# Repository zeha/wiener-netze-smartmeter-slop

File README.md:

# Wiener Netze smart meter for ESPHome

An [ESPHome](https://esphome.io) external component, `wiener_netze`, that reads the
customer interface (Kundenschnittstelle) of the Wiener Netze M1 smart meter
(Iskraemeko, also Landis+Gyr E450 with the same frame layout) through its IR
window, decrypts the push telegrams and exposes the values to Home Assistant.

The meter pushes an encrypted DLMS/COSEM telegram in an HDLC frame (105 bytes)
about once per second, receive only, 9600 baud 8N1. The component:

- waits for the `7E A0` frame start and collects 105 bytes,
- checks the CRC-16/X-25 frame checksum,
- decrypts the payload with AES-128 (CTR, which is GCM without the tag check)
  using your security key; the IV is the system title (frame bytes 14..21) plus
  the frame counter (bytes 24..27) plus `00 00 00 02`,
- reads the meter time and eight registers at fixed offsets and publishes them,
- drops frames whose decrypted timestamp is not plausible (typically a wrong key),
- logs one warning if no valid telegram arrived within `read_timeout` after boot.

The logic is a port of [aldadic/esp-smartmeter-reader](https://github.com/aldadic/esp-smartmeter-reader)
(GPL-3.0); see [LICENSE](LICENSE).

## Hardware

- Wemos (LOLIN) S2 Mini: ESP32-S2, 4 MB flash, 2 MB PSRAM. ESPHome board id `lolin_s2_mini`.
- A passive IR read head (phototransistor, 3.3 V logic), e.g. the common "IR Lesekopf TTL" types.

| IR head | S2 Mini |
|---------|---------|
| VCC     | 3V3     |
| GND     | GND     |
| Data out of the head (Hichi IR TTL: yellow wire) | GPIO11 |

No TX line is needed: the meter only sends; the head's transmit input (Hichi:
green wire) stays unconnected. ESPHome enables no pull-up on the RX pin by
itself, so the config turns on the internal one (`mode: {input: true, pullup:
true}`). If nothing arrives at all, the head may output an inverted signal; set
`inverted: true` on the `rx_pin` (see the example config). With the
[power dock](hardware/power-dock/README.md) the head's supply is switched by
GPIO5 (low = on); the example config turns it on at boot. The S2 Mini logs over
its native USB port, so the hardware UART is free for the meter.

### Battery voltage divider

The example config measures the battery of the 7000 mAh LiPo:

| Part | Connection |
|------|------------|
| R1 = 1 MOhm | battery + terminal -> GPIO3 |
| R2 = 1 MOhm | GPIO3 -> GND |
| C = 100 nF (optional) | GPIO3 -> GND, against noise |

GPIO3 is on ADC1, which keeps working while WiFi is on (ADC2 does not). The
divider halves the cell voltage (4.2 V full -> 2.1 V at the pin), inside the
range of the 12 dB attenuation. Tap the battery's own + terminal, before any
regulator. Do not measure the board's 3V3 pin or rail: it is regulated, so it
reads about 3.3 V until the battery is almost empty and says nothing about the
charge. Also, never connect a LiPo (up to 4.2 V) straight to the 3V3 pin. Feed
it through a regulator to 3V3, or into the 5V/VBUS pin and the on-board LDO.

The divider draws about 2 uA continuously (4.2 V / 2 MOhm), negligible against
7000 mAh. With 1 MOhm resistors the source is high-impedance; the 100 nF
capacitor gives the ADC a stable charge to sample and makes readings noticeably
steadier.

## Configuration

See [config/example_smartmeter.yaml](config/example_smartmeter.yaml) for a complete device.

```yaml
external_components:
  - source: github://zeha/wiener-netze-smartmeter-slop@main
    components: [wiener_netze]

uart:
  id: meter_uart
  rx_pin:
    number: GPIO11
    mode:
      input: true
      pullup: true
  baud_rate: 9600

wiener_netze:
  uart_id: meter_uart
  security_key: "0123456789abcdef0123456789abcdef"  # placeholder: your key from the portal
  read_timeout: 10s        # optional, default 10s
  on_telegram:             # optional, runs after every decoded telegram
    - logger.log: "telegram"

sensor:
  - platform: wiener_netze
    type: energy_active_plus
    name: "Energy import"

text_sensor:
  - platform: wiener_netze
    type: timestamp
    name: "Meter time"
```

The security key (32 hex characters, "Schlüssel" for the customer interface) is
shown in the Wiener Netze Smart Meter portal after the interface has been
activated. Keep it in `secrets.yaml` (`security_key: !secret meter_key`).

### Sensor types

| `type` | Unit | Device class | State class |
|--------|------|--------------|-------------|
| `energy_active_plus` (+A, import) | kWh | energy | total_increasing |
| `energy_active_minus` (-A, export) | kWh | energy | total_increasing |
| `energy_reactive_plus` (+R) | kvarh | reactive_energy | total_increasing |
| `energy_reactive_minus` (-R) | kvarh | reactive_energy | total_increasing |
| `power_active_plus` (+P) | W | power | measurement |
| `power_active_minus` (-P) | W | power | measurement |
| `power_reactive_plus` (+Q) | var | reactive_power | measurement |
| `power_reactive_minus` (-Q) | var | reactive_power | measurement |
| `telegram_count` | | | total_increasing (diagnostic; resets on every boot/wake) |

Text sensor `type: timestamp` (default): meter time as `YYYY-MM-DD HH:MM:SS`
(local meter time, no time zone).

The meter sends energy in Wh/varh; the component divides by 1000, as the
reference sketch does. All of these are standard ESPHome sensors, so filters,
names and ids work as usual. ESPHome sensor values are 32-bit floats: above
about 16 777 kWh the import counter loses its last Wh digit.

## Battery operation

The example sleeps with `deep_sleep` and wakes every 5 minutes (`sleep_duration`;
1 to 10 minutes are sensible). One telegram per wake-up is enough since the
meter pushes about every second. The `on_telegram` automation waits until Home
Assistant is connected, then puts the board back to sleep; `run_duration: 40s`
is the fallback when no telegram or no WiFi comes. To keep the wake time short:

- use a static IP (`manual_ip`) and `fast_connect: true`,
- keep the logger at `INFO` or lower once it works,
- the S2 Mini has a power LED and a USB regulator with quiescent current; for
  long battery life power it from a LiPo through an efficient 3.3 V regulator to
  the 3V3 pin, and consider removing the power LED (see the voltage divider
  above for measuring the battery).

Battery sensors: `Smartmeter battery voltage` (V) is sampled once per wake-up,
right after boot (`esphome.on_boot` at priority 500, before WiFi starts), as
the average of 64 ADC readings multiplied by 2 for the divider.
`Smartmeter battery level` (%) maps that voltage with a rough LiPo curve:
>= 4.15 V 100 %, 4.05 V 85 %, 3.95 V 70 %, 3.85 V 55 %, 3.75 V 40 %,
3.65 V 25 %, 3.55 V 12 %, 3.45 V 5 %, below 0 %. Under WiFi transmit load the
cell sags a little, and the ESP32 ADC is accurate to only a few percent, so
treat both values as estimates, good enough as a reminder to recharge.

The energy sensors are `total_increasing`, so gaps while the board sleeps do not
disturb Home Assistant's energy dashboard. To flash a sleeping board over the
air, turn on OTA mode by preventing sleep (e.g. a `deep_sleep.prevent` from a
Home Assistant helper), or flash it over USB.

## Development

See [AGENTS.md](AGENTS.md). The test in [test/](test/) checks the frame logic
against a synthetic telegram; [test/README.md](test/README.md) explains how to
capture a real one.

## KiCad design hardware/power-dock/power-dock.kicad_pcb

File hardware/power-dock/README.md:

# Power dock v1

Two-layer 32 x 28 mm add-on board: TP4056 charger for the Olimex 7000 mAh LiPo,
1 M / 1 M battery divider and an AO3401 high-side gate for the Hichi IR head.
The WEMOS S2-Mini is not on the board; it is wired to P1. Design brief: `SPEC.md`.

## Deviations from SPEC.md v1

- **USB-C pads.** The spec puts VBUS on `A12B1` + `B9A4` and CC on `A9B4`.
  In the JLC footprint `A12B1`/`B12A1` are the outer GND pins and
  `A9B4`/`B9A4` are VBUS, so following the spec would short VBUS to GND.
  The board uses VBUS = `A9B4` + `B9A4`, GND = `A12B1` + `B12A1` + shell,
  CC1 = `A5`, CC2 = `B5`.
- **Second CC resistor R7.** CC1 and CC2 are separate pads. Each one gets its
  own 5.1 k Rd (R1 on CC1, R7 on CC2). Without them a USB-C charger never
  turns VBUS on. That adds one row to `BOM.csv` (same part as R1, C14677).
- **Charge LED direction.** CHRG is open-drain and pulls low, so D1 anode goes to
  VCC_3V3 and the cathode goes through R3 to CHRG (net CHRG_LED between R3
  and D1). The spec's orientation would leave the LED reverse-biased.
- J2 sits at the bottom edge with the cable exiting downward. On the top side
  of the board this puts pin 1 (+) on the **left**, not the right.
- **Optional second battery (J3/F2, added 2026-11-10):** a second identical
  JST-PH socket next to J2 (silkscreen "BATT2") with its own 1 A PTC (F2),
  paralleling a second Olimex 7000 mAh pack for ~14 Ah / double runtime.
  Charging stays 500 mA total, so two packs take twice as long to full.
  J3 and F2 may be left unpopulated (mark them DNP in KiCad so DRC ignores
  the pads); the board then works as the single-battery dock.
- U1 uses the plain SOIC-8 footprint the spec lists, so the TP4056 exposed pad
  is not soldered. That is fine at 500 mA.
- Board is 28 mm tall, not 26 mm, so P1 and P2 fit stacked on the right edge.
- Project hole clearance is 0.2 mm (KiCad default 0.25 mm). The JLC USB-C
  footprint has 0.204 mm between its GND pads and the NPTH pegs.
- Part values show on the fab layer. The silkscreen carries references,
  pin-1 marks and "PWR DOCK".

## Assembly (JLCPCB)

Order with the gerber zip (`out/gerbers/`), `BOM.csv` and
`out/power-dock-pos.csv` (top side only). Check the USB-C, JST and LED
rotations in the JLC preview. The headers and JST are THT, so either use
JLC THT assembly or hand-solder them.

- **Battery J2:** Olimex pack red wire = + = pin 1 (marked on silkscreen).
  The plug is unmarked, so check polarity with a meter before plugging in.
- **Battery J3 (optional):** same pack type, wired the same way (red = + =
  pin 1, "BATT2" + polarity marks on silkscreen). Leave the socket and the
  F2 PTC unpopulated for the single-battery dock; populate both to run two
  packs in parallel (~14 Ah).
- **P1 to S2-Mini jumpers:** P1.1 -> 5V/VBUS, P1.2 -> GND, P1.3 -> IO3,
  P1.4 -> 3V3, P1.5 -> IO5, P1.6 -> IO11 (UART RX; the config enables the internal
  pull-up on it).
- **P2 Hichi IR head:** 1 = switched 3V3, 2 = GND, 3 = the head's data output
  (yellow wire), 4 = not connected (the green wire, the head's transmit input,
  is not needed). Go by wire colour: Hichi labels its pads from the
  microcontroller's side ("TX to TX, RX to RX, not crossed").
- **Charge LED D1:** lights while the TP4056 is charging and goes out when
  charging ends (C/10 = 50 mA) or with no USB. It runs from the S2-Mini 3V3
  rail, so it only lights while the S2-Mini is powered.
- **Charge current:** R2 = 2.4 k sets 500 mA.
- **Battery voltage:** GPIO3 (ADC1_CH0) reads BAT+/2 through R5/R6. Multiply
  by 2 (the ESPHome config already does this). A 3.0-4.2 V cell gives 1.5-2.1 V.
- **IR head gate:** GPIO5 low = head on. R4 holds the gate high, so the head
  is off by default.

## Regenerate and check

```sh
scripts/run.sh                       # writes .kicad_sch, .kicad_sym, .kicad_pcb
K=/opt/data/cache/kicad/AppDir/usr/bin/kicad-cli
$K sch erc power-dock.kicad_sch
$K pcb drc --schematic-parity --refill-zones --save-board power-dock.kicad_pcb
$K sch export netlist -o out/power-dock.sch.net power-dock.kicad_sch
SCRIPT=scripts/compare_netlists.py scripts/run.sh out/power-dock.sch.net power-dock.kicad_pcb
```

Edit placement and routing in `scripts/build.py` (`PLACE`, `ROUTES`, `VIAS`),
not in the generated files.

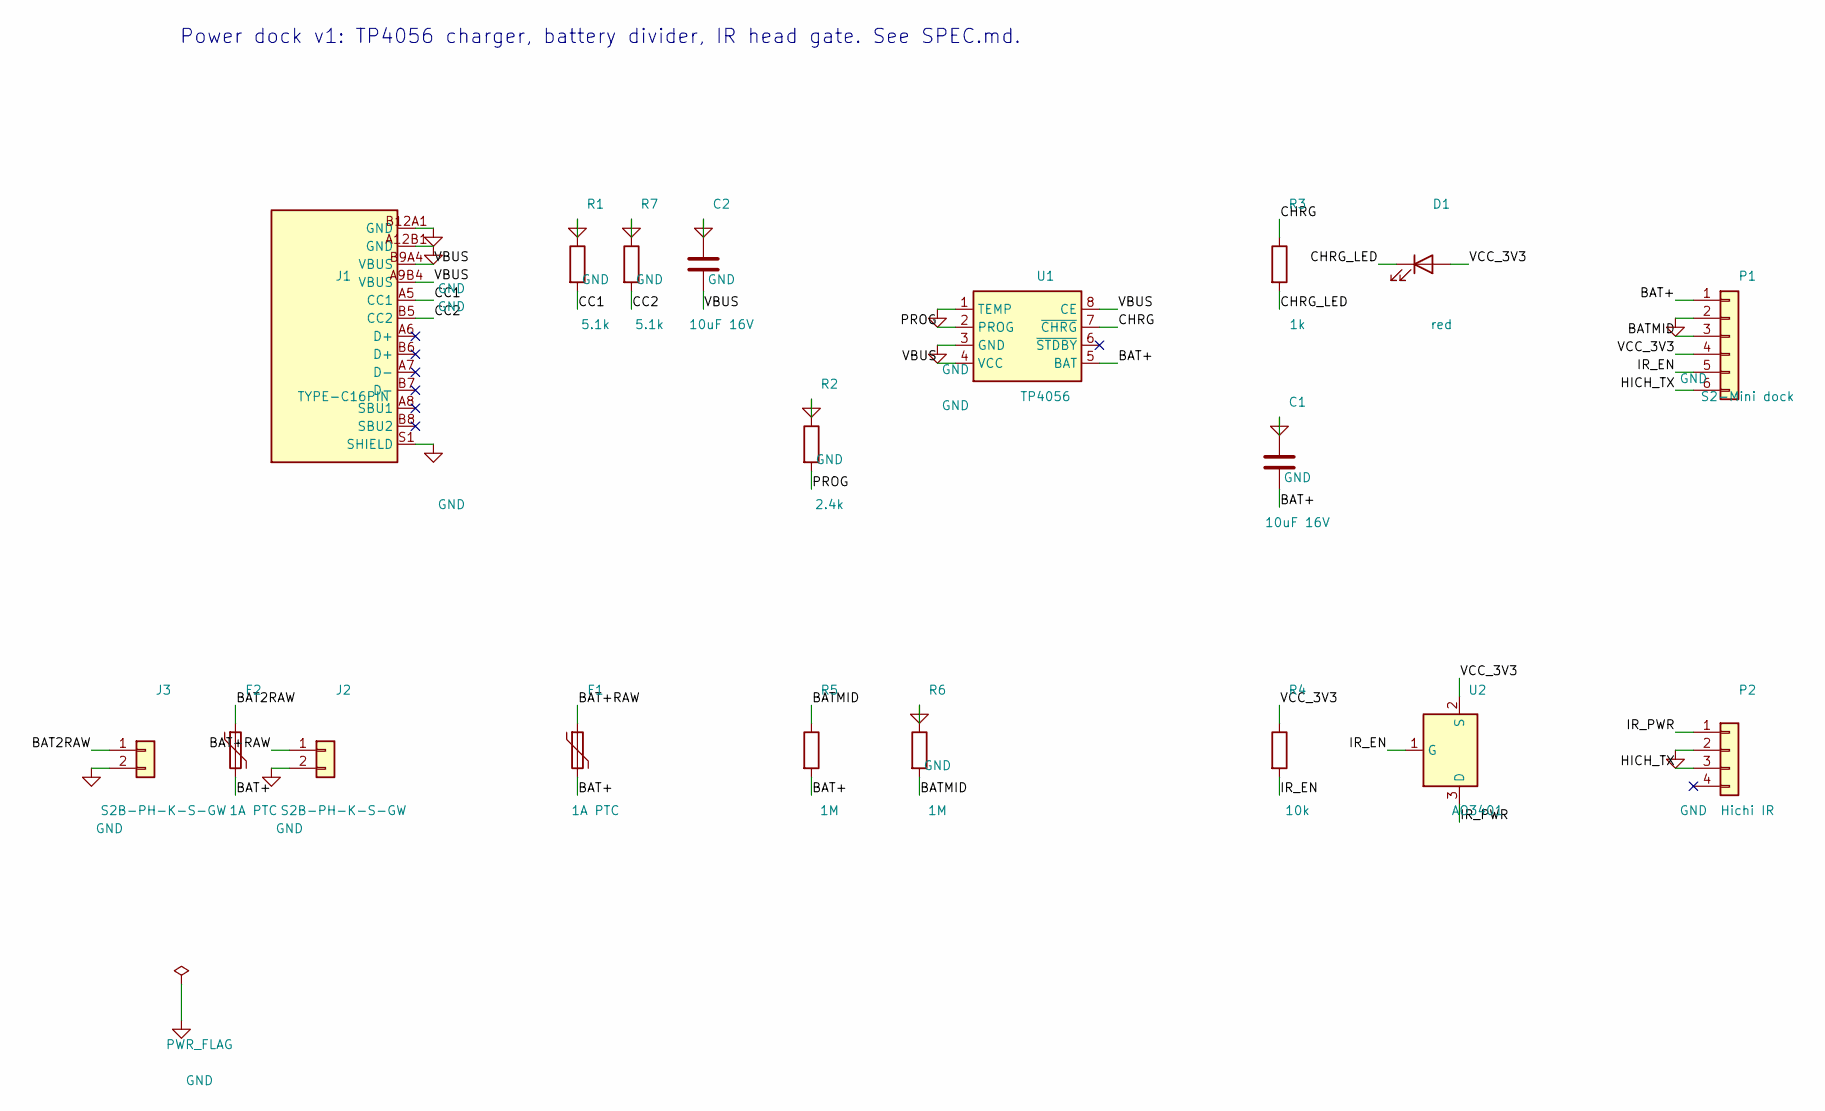
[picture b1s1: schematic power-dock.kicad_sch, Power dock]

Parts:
C1, C2: 10uF 16V; C_0603_1608Metric; MPN 0603X106M160NT; LCSC C108340
D1: red; LED_0603_1608Metric; MPN YLED0603R; LCSC C19171390
F1, F2: 1A PTC; R_0805_2012Metric; MPN SMD0805-100C-6V; LCSC C22472456
J1: TYPE-C16PIN; TYPE-C-SMD_HX-TYPE-C-16PIN; MPN TYPE-C16PIN; LCSC C393939
J2, J3: S2B-PH-K-S-GW; JST_PH_S2B-PH-K_1x02_P2.00mm_Horizontal; MPN S2B-PH-K-S-GW; LCSC C157932
P1: S2-Mini dock; PinHeader_1x06_P2.54mm_Vertical; MPN 2.54-1*6; LCSC C5156615
P2: Hichi IR; PinHeader_1x04_P2.54mm_Vertical; MPN 2.54-1*4; LCSC C5116483
R1, R7: 5.1k; R_0603_1608Metric; MPN RC0603JR-075K1L; LCSC C14677
R2: 2.4k; R_0603_1608Metric; MPN RC0603JR-072K4L; LCSC C127450
R3: 1k; R_0603_1608Metric; MPN RC0603JR-071KL; LCSC C14676
R4: 10k; R_0603_1608Metric; MPN RC0603JR-0710KL; LCSC C99198
R5, R6: 1M; R_0603_1608Metric; MPN RC0603JR-071ML; LCSC C107698
U1: TP4056; SOIC-8_3.9x4.9mm_P1.27mm; MPN TP4056; LCSC C725790
U2: AO3401; SOT-23; MPN AO3401; LCSC C727156

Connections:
/BAT2RAW: F2.1, J3.1
/BAT+: C1.2, F1.2, F2.2, P1.1, R5.2, U1.5 (BAT)
/BAT+RAW: F1.1, J2.1
/BATMID: P1.3, R5.1, R6.2
/CC1: J1.A5 (CC1), R1.2
/CC2: J1.B5 (CC2), R7.2
/CHRG: R3.1, U1.7 (~CHRG)
/CHRG_LED: D1.1 (K), R3.2
/HICH_TX: P1.6, P2.3
/IR_EN: P1.5, R4.2, U2.1 (G)
/IR_PWR: P2.1, U2.3 (D)
/PROG: R2.2, U1.2 (PROG)
/VBUS: C2.2, J1.A9B4 (VBUS), J1.B9A4 (VBUS), U1.4 (VCC), U1.8 (CE)
/VCC_3V3: D1.2 (A), P1.4, R4.1, U2.2 (S)
GND: C1.1, C2.1, J1.A12B1 (GND), J1.B12A1 (GND), J1.S1 (SHIELD), J2.2, J3.2, P1.2, P2.2, R1.1, R2.1, R6.1, R7.1, U1.1 (TEMP), U1.3 (GND)

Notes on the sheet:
Power dock v1: TP4056 charger, battery divider, IR head gate. See SPEC.md.

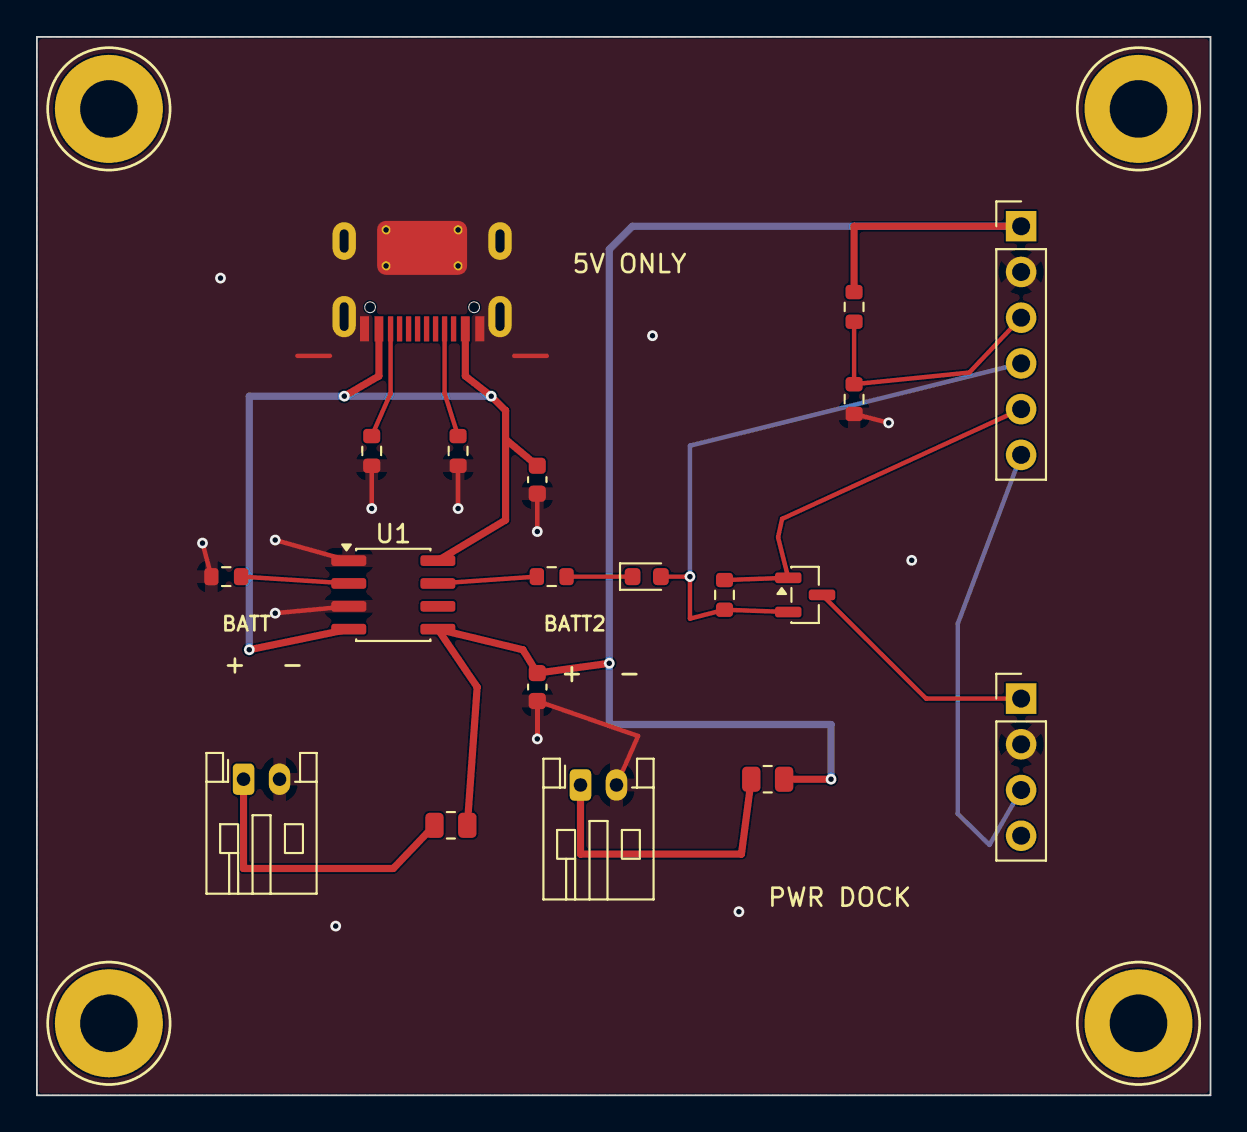
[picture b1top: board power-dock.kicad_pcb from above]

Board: 2 copper layers, 65.2 x 58.8 mm, 23 parts (0 on the bottom side), 15 nets.

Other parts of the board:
MH1, MH2, MH3, MH4: 3.2mm; MountingHole_3.2mm_Pad

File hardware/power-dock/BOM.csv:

Reference,Qty,Value,Package,LCSC,MPN,Manufacturer
U1,1,TP4056,ESOP-8 (SOIC-8 3.9x4.9 P1.27),C725790,TP4056,UMW (Youtai)
U2,1,AO3401,SOT-23 (1=G 2=S 3=D),C727156,AO3401,TWGMC
J1,1,USB-C 16 pin,SMD USB-C (JLC footprint),C393939,TYPE-C16PIN,SHOU HAN
J2,1,JST-PH 2P,"JST-PH 2.0 mm, right-angle",C157932,S2B-PH-K-S-GW,JST
J3,1,JST-PH 2P (optional 2nd battery),"JST-PH 2.0 mm, right-angle",C157932,S2B-PH-K-S-GW,JST
F1,1,PTC 1A,0805,C22472456,SMD0805-100C-6V,BNstar
F2,1,PTC 1A (optional 2nd battery),0805,C22472456,SMD0805-100C-6V,BNstar
R1,1,5.1k,0603,C14677,RC0603JR-075K1L,YAGEO
R7,1,5.1k,0603,C14677,RC0603JR-075K1L,YAGEO
R2,1,2.4k,0603,C127450,RC0603JR-072K4L,YAGEO
R3,1,1k,0603,C14676,RC0603JR-071KL,YAGEO
R4,1,10k,0603,C99198,RC0603JR-0710KL,YAGEO
R5,1,1M,0603,C107698,RC0603JR-071ML,YAGEO
R6,1,1M,0603,C107698,RC0603JR-071ML,YAGEO
C1,1,10uF 16V,0603,C108340,0603X106M160NT,FH
C2,1,10uF 16V,0603,C108340,0603X106M160NT,FH
D1,1,red LED,0603,C19171390,YLED0603R,YONGYUTAI
P1,1,1x6 header,1x6 2.54 mm THT,C5156615,2.54-1*6,ZHOURI
P2,1,1x4 header,1x4 2.54 mm THT,C5116483,2.54-1*4,ZHOURI
